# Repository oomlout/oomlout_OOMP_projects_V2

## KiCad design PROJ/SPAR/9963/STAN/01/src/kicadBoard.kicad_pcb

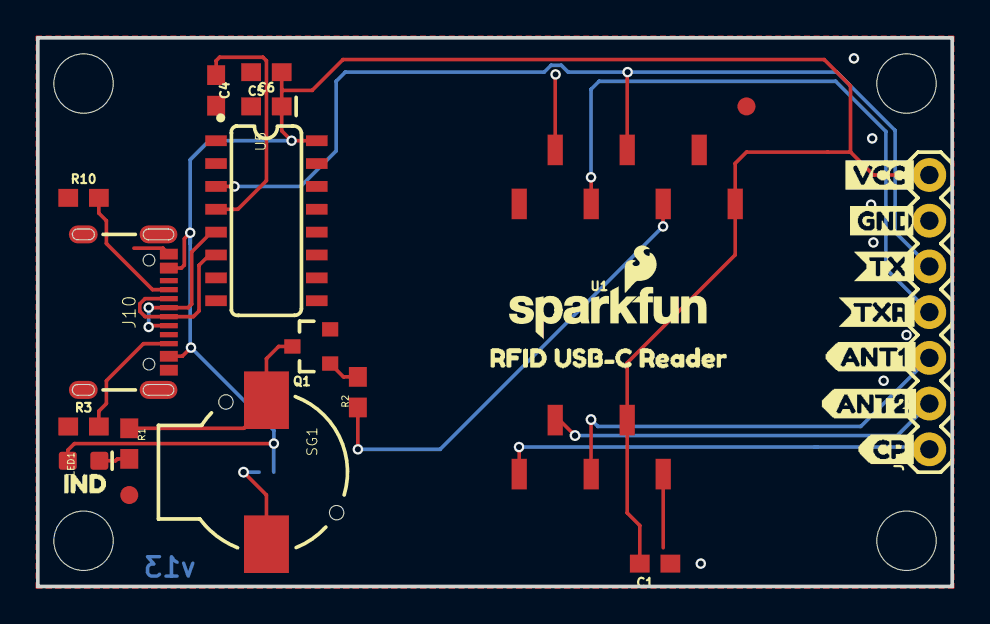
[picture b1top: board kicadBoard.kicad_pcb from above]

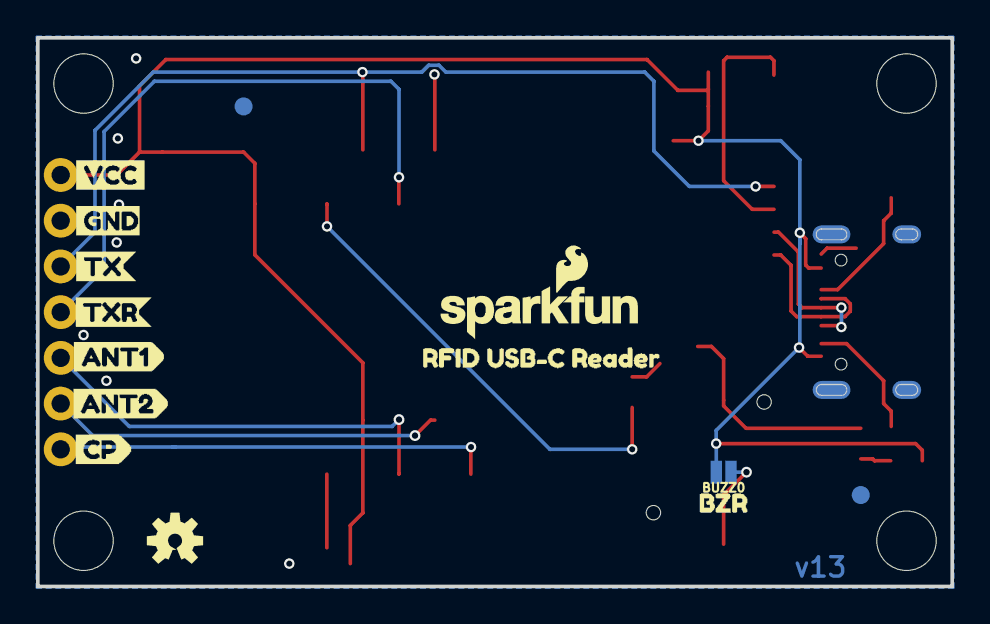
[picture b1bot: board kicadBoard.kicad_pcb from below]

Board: 2 copper layers, 50.8 x 30.5 mm, 47 parts (14 on the bottom side), 17 nets.

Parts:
BUZZ0: buzz; SMT-JUMPER_2_NO_NO-SILK
C1: 2.2uF; 0603
C4: 10nF; 0603
C5: 470nF; 0603
C6: 10uF; 0603-POLAR
FRAME1: FRAME-LETTER; CREATIVE_COMMONS
J1: 1X07
J10: USB-C-16P
JP1, JP2, JP3, JP5: FIDUCIAL1X2; FIDUCIAL-1X2
LED1: BLUE; LED-0603
LOGO1, LOGO2: SFE_LOGO_NAME_FLAME.1_INCH; SFE_LOGO_NAME_FLAME_.1
LOGO3: OSHW-LOGOS; OSHW-LOGO-S
LOGO4: REVISION
Q1: 600mA/40V; SOT23-3
R1: 330; 0603
R2: 180; 0603
R3, R10: 5.1k; 0603
SG1: BUZZER-SMD; BUZZER-CCV
U1: ID-12/20SMD; ID-12_SMD
U5: CH340C; SO016
U$1: CP5
U$3, U$13: GND1
U$4, U$5, U$6, U$7: STAND-OFF
U$8: BZR3
U$9: TX3
U$10: TXR4
U$11, U$12: VCC0
U$14: TX0
U$15: TXR1
U$16: CP2
U$17, U$18: RFID_USB#C_READER0
U$19: ANT11
U$20: ANT13
U$21: ANT22
U$22: ANT24
U$23: IND0

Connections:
ANT1: J1.3, U1.3
ANT2: J1.2, U1.4
CP: J1.1, U1.5
GND: C1.1, C4.2, C5.2, C6.-, J1.6, J10.GND, J10.GND2, Q1.2, R3.1, R10.1, U1.1, U1.7, U5.1
INDICATOR: R2.1, U1.10
unnamed: Q1.3, R1.1, SG1.-
unnamed: C4.1, U5.4
unnamed: J10.A6, J10.B6, U5.5
unnamed: BUZZ0.1, SG1.+
unnamed: J10.A5, R10.2
unnamed: LED1.C, R1.2
unnamed: Q1.1, R2.2
unnamed: J10.A7, J10.B7, U5.6
unnamed: J10.B5, R3.2
TX-O: J1.5, U1.9, U5.3
TX-O-RS232: J1.4, U1.8
VCC: BUZZ0.2, C1.2, C5.1, C6.+, J1.7, J10.VBUS1, J10.VBUS2, LED1.A, U1.2, U1.11, U5.16

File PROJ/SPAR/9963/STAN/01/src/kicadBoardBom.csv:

"Id";"Designator";"Package";"Quantity";"Designation";"Supplier and ref";
1;"U5";"SO016";1;"CH340C";;;
2;"U$7,U$5,U$6,U$4";"STAND-OFF";4;"STAND-OFF";;;
3;"J1";"1X07";1;"";;;
4;"R10,R3";"0603";2;"5.1k";;;
5;"LOGO4";"REVISION";1;"REVISION";;;
6;"C5";"0603";1;"470nF";;;
7;"U$1";"CP5";1;"";;;
8;"U$21";"ANT22";1;"";;;
9;"R2";"0603";1;"180";;;
10;"SG1";"BUZZER-CCV";1;"BUZZER-SMD";;;
11;"FRAME1";"CREATIVE_COMMONS";1;"FRAME-LETTER";;;
12;"C4";"0603";1;"10nF";;;
13;"LED1";"LED-0603";1;"BLUE";;;
14;"U1";"ID-12_SMD";1;"ID-12/20SMD";;;
15;"C6";"0603-POLAR";1;"10uF";;;
16;"J10";"USB-C-16P";1;"";;;
17;"C1";"0603";1;"2.2uF";;;
18;"JP2,JP3,JP1,JP5";"FIDUCIAL-1X2";4;"FIDUCIAL1X2";;;
19;"R1";"0603";1;"330";;;
20;"U$3,U$13";"GND1";2;"";;;
21;"LOGO1,LOGO2";"SFE_LOGO_NAME_FLAME_.1";2;"SFE_LOGO_NAME_FLAME.1_INCH";;;
22;"U$17,U$18";"RFID_USB#C_READER0";2;"";;;
23;"U$19";"ANT11";1;"";;;
24;"U$23";"IND0";1;"";;;
25;"U$9";"TX3";1;"";;;
26;"Q1";"SOT23-3";1;"600mA/40V";;;
27;"U$10";"TXR4";1;"";;;
28;"U$11,U$12";"VCC0";2;"";;;
29;"U$8";"BZR3";1;"";;;
30;"BUZZ0";"SMT-JUMPER_2_NO_NO-SILK";1;"buzz";;;
31;"U$20";"ANT13";1;"";;;
32;"U$16";"CP2";1;"";;;
33;"U$15";"TXR1";1;"";;;
34;"U$22";"ANT24";1;"";;;
35;"LOGO3";"OSHW-LOGO-S";1;"OSHW-LOGOS";;;
36;"U$14";"TX0";1;"";;;

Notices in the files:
parts and their libraries:
HTTPS://CREATIVECOMMONS.ORG/LICENSES/BY-SA/4.0
RELEASED UNDER THE CREATIVE COMMONS ATTRIBUTION SHARE-ALIKE 4.0 LICENSE
